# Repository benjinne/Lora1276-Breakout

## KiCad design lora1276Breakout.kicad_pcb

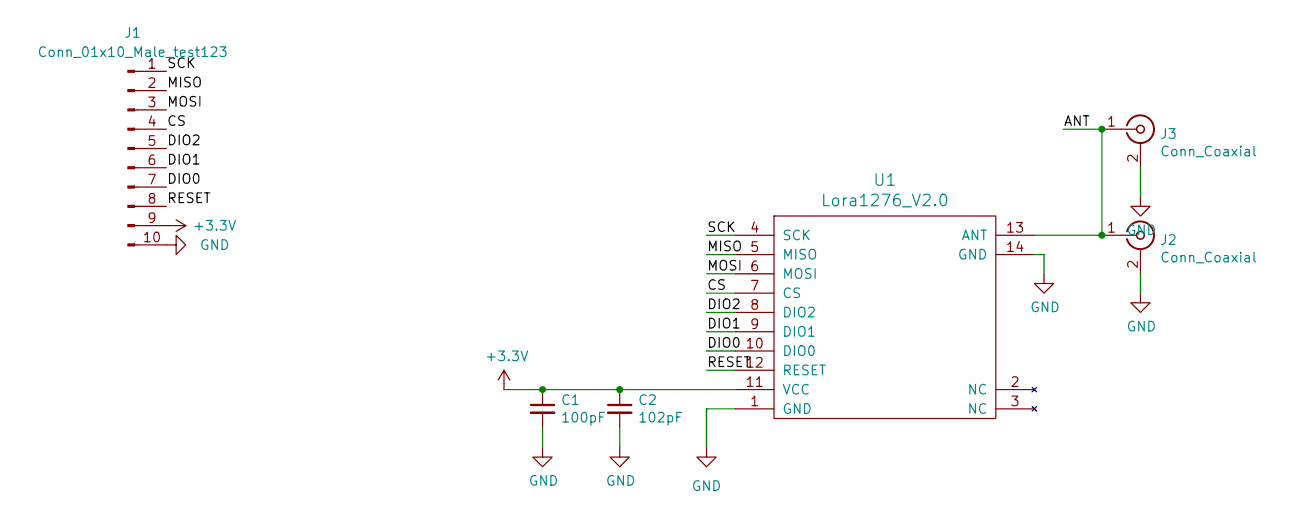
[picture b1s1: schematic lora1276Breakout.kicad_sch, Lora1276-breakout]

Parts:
C1: 100pF; C_0805_2012Metric
C2: 102pF; C_0805_2012Metric
J1: Conn_01x10_Male_test123; PinHeader_1x10_P2.54mm_Vertical
J2: Conn_Coaxial; SMA_Molex_73251-1153_EdgeMount_Horizontal
J3: Conn_Coaxial; U.FL_Hirose_U.FL-R-SMT-1_Vertical
U1: Lora1276_V2.0

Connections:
+3V3: C1.1, C2.1, J1.9, U1.11 (VCC)
/CS: J1.4, U1.7 (CS)
/DIO0: J1.7, U1.10 (DIO0)
/DIO1: J1.6, U1.9 (DIO1)
/DIO2: J1.5, U1.8 (DIO2)
/MISO: J1.2, U1.5 (MISO)
/MOSI: J1.3, U1.6 (MOSI)
/RESET: J1.8, U1.12 (RESET)
/SCK: J1.1, U1.4 (SCK)
GND: C1.2, C2.2, J1.10, J2.2 (Ext), J3.2 (Ext), U1.1 (GND), U1.14 (GND)
unnamed: J2.1 (In), J3.1 (In), U1.13 (ANT)

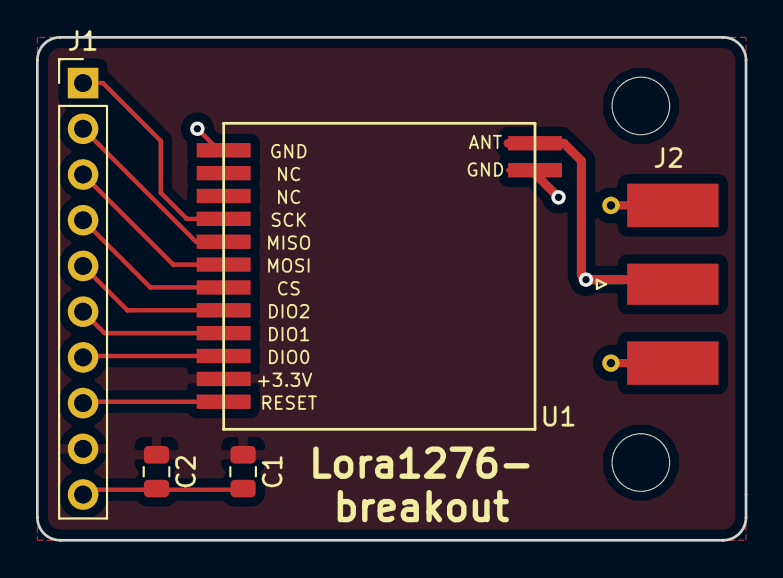
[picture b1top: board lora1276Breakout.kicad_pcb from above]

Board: 2 copper layers, 39.4 x 27.9 mm, 6 parts (1 on the bottom side), 11 nets.

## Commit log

2023-01-09 update to latest kicad and small changes
